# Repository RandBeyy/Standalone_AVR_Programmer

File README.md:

This project is based on Nick Gammon's ATmega_Hex_Uploader.
I added the LCD2004 to the project and design PCB so this device look more decent.
The main reason of this project is to make a small device to program a lot of MCUs like Attiny45
with simple and easy interface and without a computer.

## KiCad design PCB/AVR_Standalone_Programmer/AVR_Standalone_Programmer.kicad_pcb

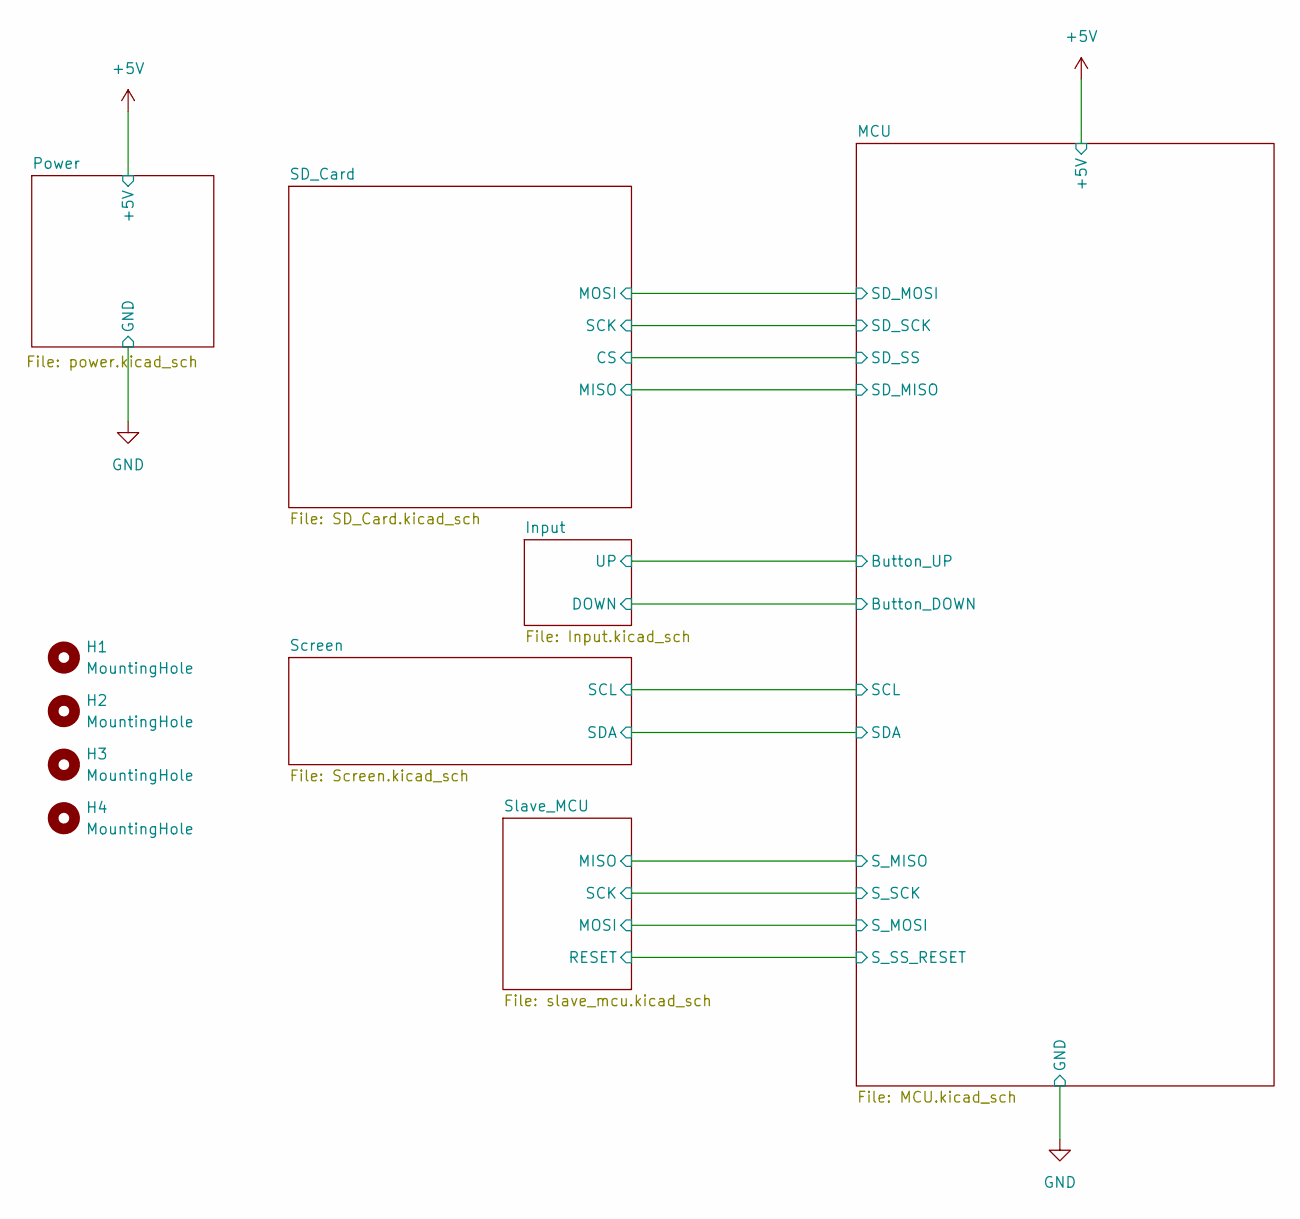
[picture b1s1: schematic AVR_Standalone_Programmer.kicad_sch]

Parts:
H1, H2, H3, H4: MountingHole; MountingHole_2.2mm_M2

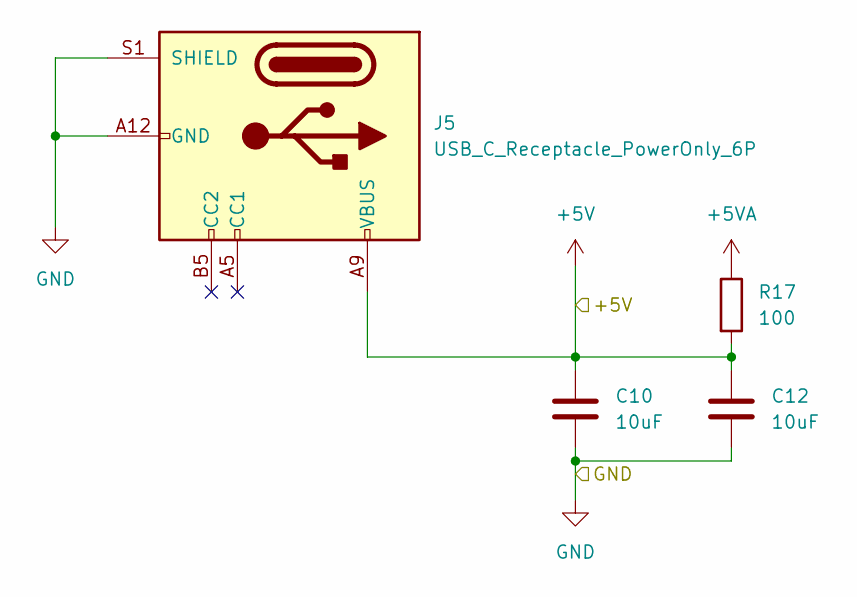
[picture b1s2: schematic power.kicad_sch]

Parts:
C10, C12: 10uF; C_0603_1608Metric
J5: USB_C_Receptacle_PowerOnly_6P; USB_C_Receptacle_GCT_USB4125-xx-x_6P_TopMnt_Horizontal
R17: 100; R_0603_1608Metric

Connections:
+5V: C10.1, C12.1, J5.A9 (VBUS), J5.B9 (VBUS), R17.2; also elsewhere on the board
+5VA: R17.1; also elsewhere on the board
GND: C10.2, C12.2, J5.A12 (GND), J5.B12 (GND), J5.S1 (SHIELD); also elsewhere on the board

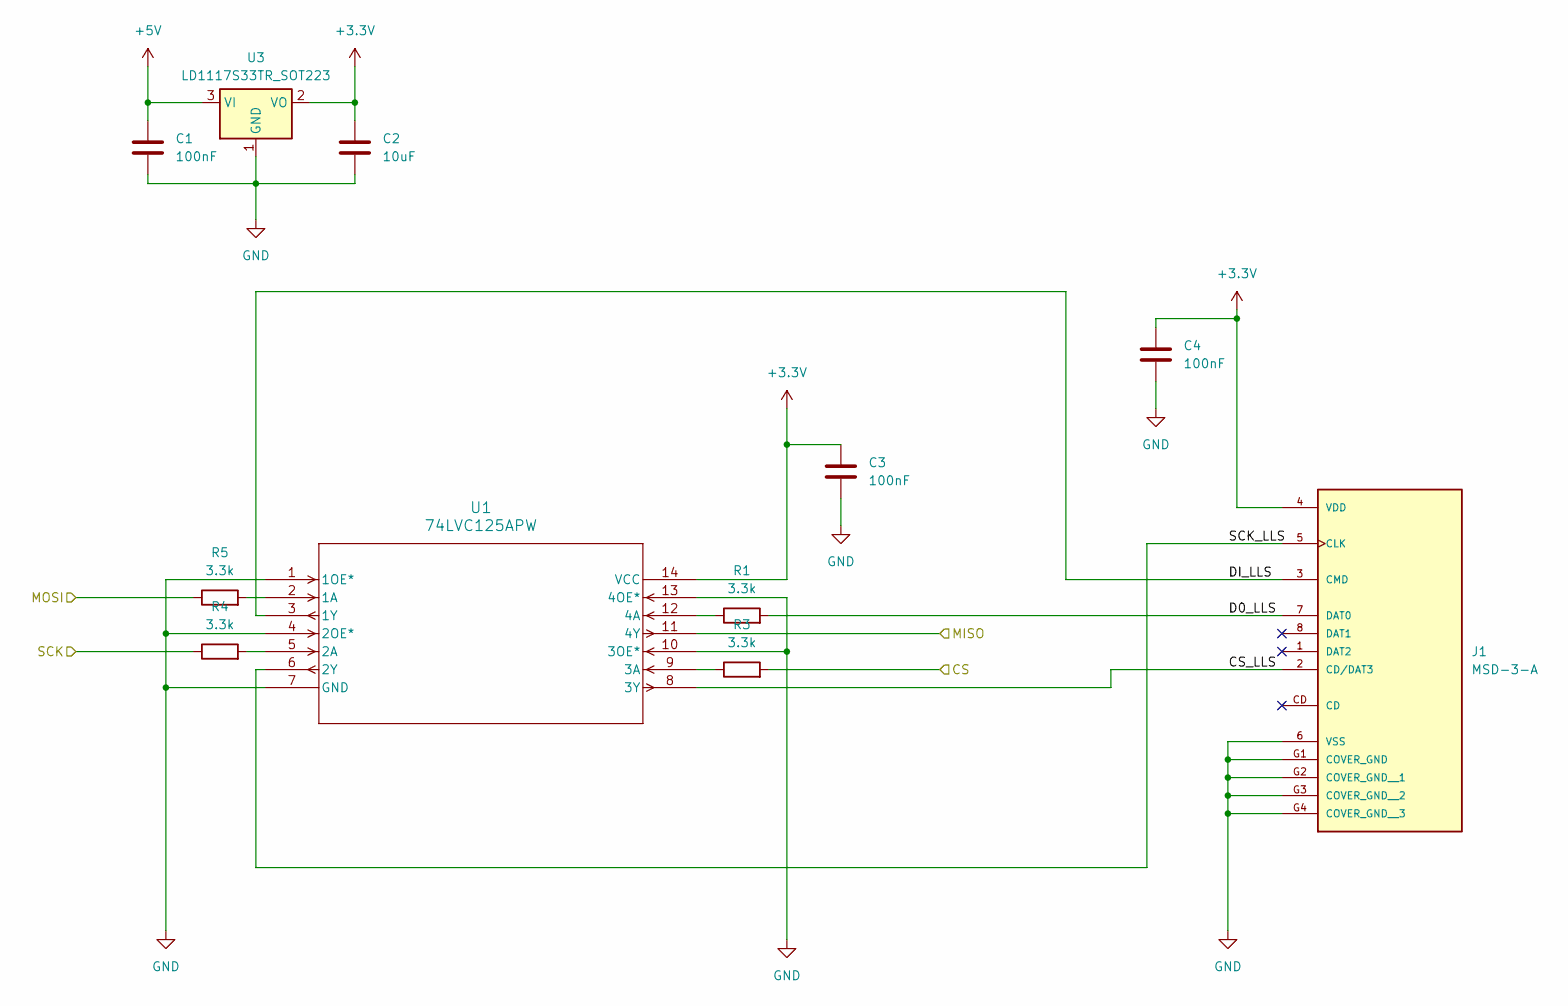
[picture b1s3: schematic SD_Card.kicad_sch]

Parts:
C1, C3, C4: 100nF; C_0603_1608Metric
C2: 10uF; C_0603_1608Metric
J1: MSD-3-A; CUI_MSD-3-A; PARTREV 1.0
R1, R3, R4, R5: 3.3k; R_0603_1608Metric
U1: 74LVC125APW; SOT402-1_NEX
U3: LD1117S33TR_SOT223; SOT-223-3_TabPin2

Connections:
+3.3V: C2.1, C3.1, C4.1, J1.4 (VDD), U1.14 (VCC), U3.2 (VO)
+5V: C1.1, U3.3 (VI); also elsewhere on the board
/MCU/MISO: U1.11 (4Y); also elsewhere on the board
/MCU/MOSI: R5.1; also elsewhere on the board
/MCU/SCK: R4.1; also elsewhere on the board
/MCU/SD_SS: R3.2; also elsewhere on the board
/SD_Card/CS_LLS: J1.2 (CD/DAT3), U1.8 (3Y)
/SD_Card/D0_LLS: J1.7 (DAT0), R1.2
/SD_Card/DI_LLS: J1.3 (CMD), U1.3 (1Y)
/SD_Card/SCK_LLS: J1.5 (CLK), U1.6 (2Y)
GND: C1.2, C2.2, C3.2, C4.2, J1.6 (VSS), J1.G1 (COVER_GND), J1.G2 (COVER_GND__1), J1.G3 (COVER_GND__2), J1.G4 (COVER_GND__3), U1.1 (1OE*), U1.4 (2OE*), U1.7 (GND), U1.10 (3OE*), U1.13 (4OE*), U3.1 (GND); also elsewhere on the board
unnamed: R5.2, U1.2 (1A)
unnamed: R4.2, U1.5 (2A)
unnamed: R3.1, U1.9 (3A)
unnamed: R1.1, U1.12 (4A)

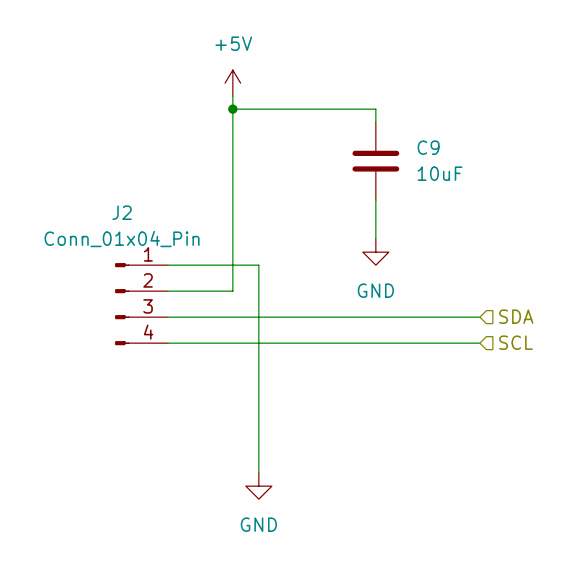
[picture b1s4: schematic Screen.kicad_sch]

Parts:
C9: 10uF; C_0603_1608Metric
J2: Conn_01x04_Pin; PinHeader_1x04_P2.54mm_Vertical

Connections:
+5V: C9.1, J2.2; also elsewhere on the board
/MCU/SCL: J2.4; also elsewhere on the board
/MCU/SDA: J2.3; also elsewhere on the board
GND: C9.2, J2.1; also elsewhere on the board

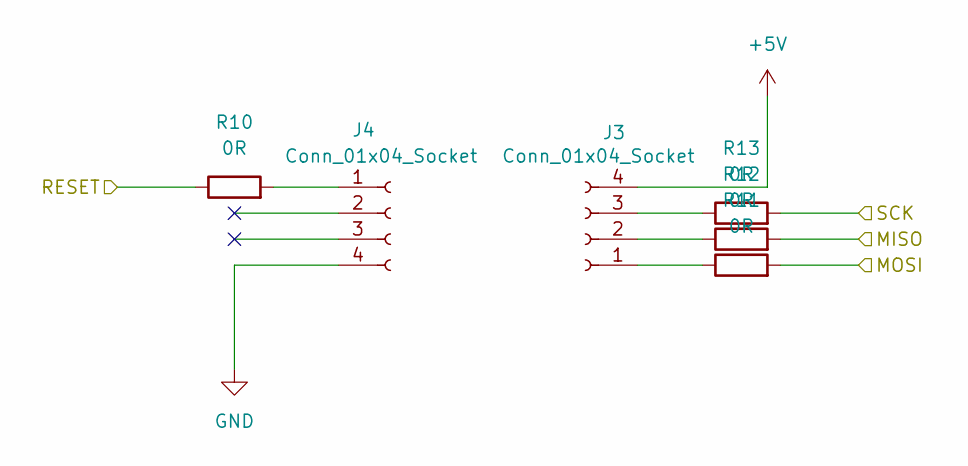
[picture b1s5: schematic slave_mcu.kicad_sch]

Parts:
J3, J4: Conn_01x04_Socket; PinSocket_1x04_P2.54mm_Vertical
R10, R11, R12, R13: 0R; R_0603_1608Metric

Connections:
+5V: J3.4; also elsewhere on the board
/MCU/S_MISO: R12.2; also elsewhere on the board
/MCU/S_MOSI: R11.2; also elsewhere on the board
/MCU/S_SCK: R13.2; also elsewhere on the board
/MCU/S_SS_RESET: R10.1; also elsewhere on the board
GND: J4.4; also elsewhere on the board
unnamed: J3.1, R11.1
unnamed: J3.2, R12.1
unnamed: J3.3, R13.1
unnamed: J4.1, R10.2

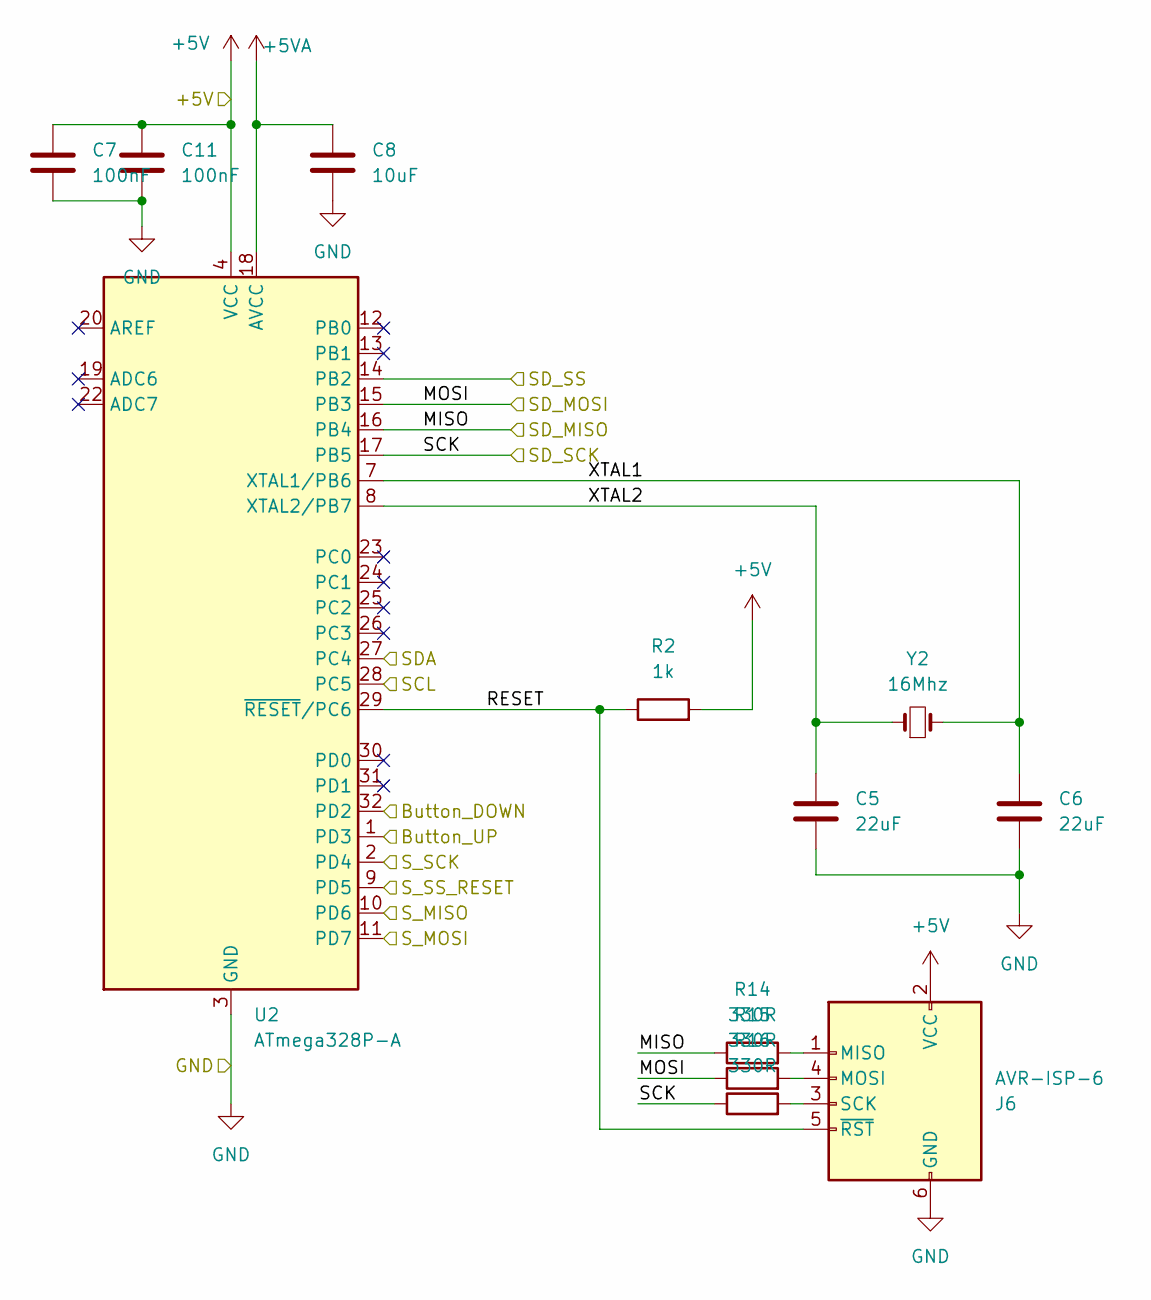
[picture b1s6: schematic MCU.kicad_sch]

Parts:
C5, C6: 22uF; C_0805_2012Metric
C7, C11: 100nF; C_0603_1608Metric
C8: 10uF; C_0603_1608Metric
J6: AVR-ISP-6; PinHeader_2x03_P2.54mm_Vertical
R2: 1k; R_0603_1608Metric
R14, R15, R16: 330R; R_0603_1608Metric
U2: ATmega328P-A; TQFP-32_7x7mm_P0.8mm
Y2: 16Mhz; Crystal_SMD_5032-2Pin_5.0x3.2mm

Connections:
+5V: C7.1, C11.1, J6.2 (VCC), R2.2, U2.4 (VCC), U2.6 (VCC); also elsewhere on the board
+5VA: C8.1, U2.18 (AVCC); also elsewhere on the board
/Input/DOWN: U2.32 (PD2); also elsewhere on the board
/Input/UP: U2.1 (PD3); also elsewhere on the board
/MCU/MISO: R14.1, U2.16 (PB4); also elsewhere on the board
/MCU/MOSI: R15.1, U2.15 (PB3); also elsewhere on the board
/MCU/RESET: J6.5 (~RST), R2.1, U2.29 (~RESET/PC6)
/MCU/SCK: R16.1, U2.17 (PB5); also elsewhere on the board
/MCU/SCL: U2.28 (PC5); also elsewhere on the board
/MCU/SDA: U2.27 (PC4); also elsewhere on the board
/MCU/SD_SS: U2.14 (PB2); also elsewhere on the board
/MCU/S_MISO: U2.10 (PD6); also elsewhere on the board
/MCU/S_MOSI: U2.11 (PD7); also elsewhere on the board
/MCU/S_SCK: U2.2 (PD4); also elsewhere on the board
/MCU/S_SS_RESET: U2.9 (PD5); also elsewhere on the board
/MCU/XTAL1: C6.1, U2.7 (XTAL1/PB6), Y2.2
/MCU/XTAL2: C5.1, U2.8 (XTAL2/PB7), Y2.1
GND: C5.2, C6.2, C7.2, C8.2, C11.2, J6.6 (GND), U2.3 (GND), U2.5 (GND), U2.21 (GND); also elsewhere on the board
unnamed: J6.1 (MISO), R14.2
unnamed: J6.4 (MOSI), R15.2
unnamed: J6.3 (SCK), R16.2

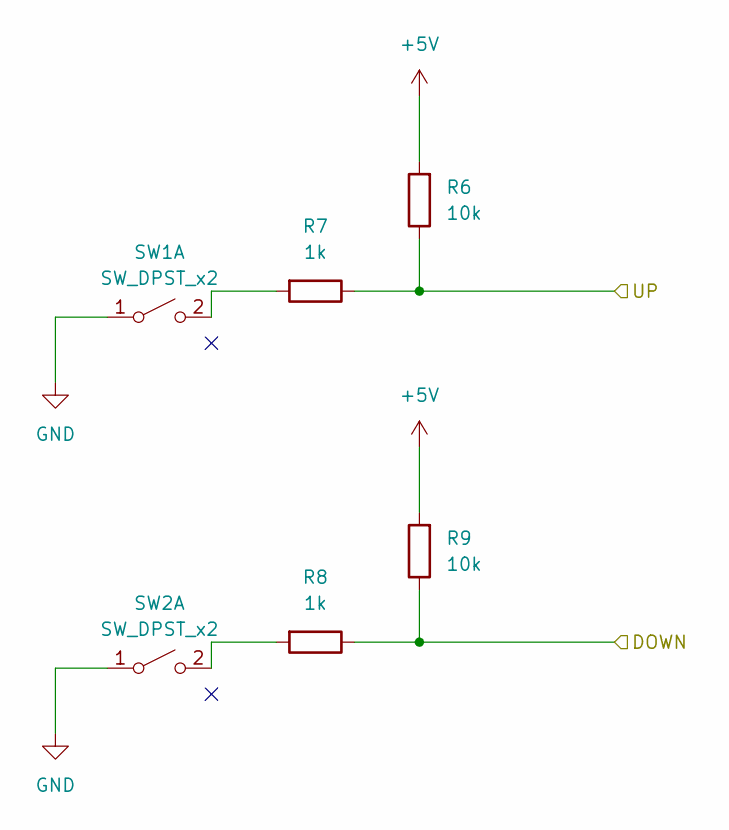
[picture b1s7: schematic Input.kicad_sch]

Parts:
R6, R9: 10k; R_0603_1608Metric
R7, R8: 1k; R_0603_1608Metric
SW1, SW2: SW_DPST_x2; SW_Push_SPST_NO_Alps_SKRK

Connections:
+5V: R6.2, R9.2; also elsewhere on the board
/Input/DOWN: R8.1, R9.1; also elsewhere on the board
/Input/UP: R6.1, R7.1; also elsewhere on the board
GND: SW1.1 (A), SW2.1 (A); also elsewhere on the board
unnamed: R7.2, SW1.2 (B)
unnamed: R8.2, SW2.2 (B)

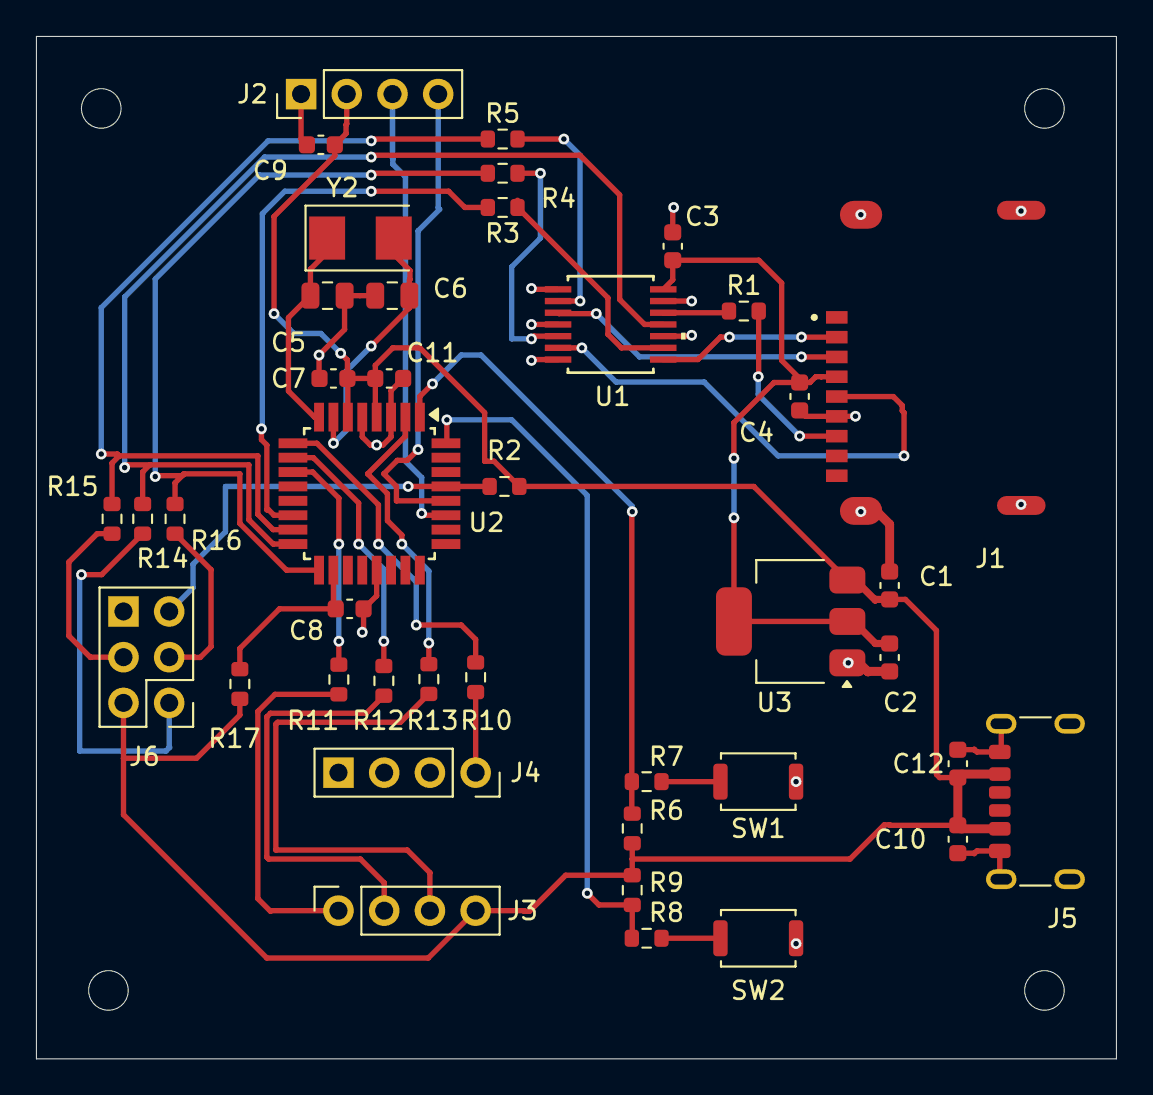
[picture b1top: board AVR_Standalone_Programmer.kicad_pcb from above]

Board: 2 copper layers, 60.0 x 56.8 mm, 45 parts (0 on the bottom side), 36 nets.

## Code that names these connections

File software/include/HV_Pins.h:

// HV_Pins.h
//
// Pin numbers and commands for high-voltage serial or parallel programming
//
// Author: Nick Gammon




#if HIGH_VOLTAGE_PARALLEL || HIGH_VOLTAGE_SERIAL

  // high-voltage programming commands we can send (when action is LOAD_COMMAND)
  enum {
        CMD_CHIP_ERASE       = 0b10000000,
        CMD_WRITE_FUSE_BITS  = 0b01000000,
        CMD_WRITE_LOCK_BITS  = 0b00100000,
        CMD_WRITE_FLASH      = 0b00010000,
        CMD_WRITE_EEPROM     = 0b00010001,
        CMD_READ_SIGNATURE   = 0b00001000,
        CMD_READ_FUSE_BITS   = 0b00000100,
        CMD_READ_FLASH       = 0b00000010,
        CMD_READ_EEPROM      = 0b00000011,
        CMD_NO_OPERATION     = 0b00000000,
        }; // end of commands

#endif // HIGH_VOLTAGE_PARALLEL || HIGH_VOLTAGE_SERIAL

#if HIGH_VOLTAGE_PARALLEL
  // pin assignments for parallel high-voltage programming
  
// Arduino pins                 Target pins
// ------------                 -----------------------
  const byte dataPins [8] = { 
    6,                        // 14 (PB0) (data bit 0)
    7,                        // 15 (PB1) (data bit 1)
    8,                        // 16 (PB2) (data bit 2)
    9,                        // 17 (PB3) (data bit 3)  
    10,                       // 18 (PB4) (data bit 4)
    11,                       // 19 (PB5) (data bit 5)  
    12,                       // 23 (PC0) (data bit 6)
    13                        // 24 (PC1) (data bit 7)
    };    // end of dataPins

  enum {                                        
      RDY     = A0,           //  3 (PD1) (low means busy)   
      OE      = A1,           //  4 (PD2) (low means output enabled)    
      WR      = A2,           //  5 (PD3) (low means write)    
      BS1     = A3,           //  6 (PD4)     
      XTAL1   = A4,           //  9 (XTAL1)     
      XA0     = A5,           // 11 (PD5)     
      XA1     =  2,           // 12 (PD6)     
      PAGEL   =  3,           // 13 (PD7)     
      BS2     =  4,           // 25 (PC2)     
      VCC     =  5,           // 7 and 20 (VCC and AVCC)
  };  // end of other pins                  
                                            
  
  /* Note: /RESET (Pin 1) is brought to 12V by connecting a transistor and MOSFET (high-side driver)
     via a RC network to (the target) VCC. R = 22k, C = 10 nF. This gives a delay of around 40 uS between
     VCC and /RESET. The transistor turns on the MOSFET, which switches +12V to /RESET.
     For transistor/MOSFET schematic see: http://www.gammon.com.au/images/Arduino/MOSFET_high_side_driver.png
     
          |------------------------------------------------------->  VCC and AVCC
          |
   D5 >---|--/\/\/\/\---|-----------> Transistor ---> MOSFET -----> /RESET
               22k      |
                       ===  10 nF
                        |
                        |
                        V
                       Gnd
       
     Also connect the grounds. Gnd to pins 8 and 22.
     Decoupling capacitors: 0.1 uF between VCC/AVCC (pins 7 and 20) and Gnd.
     Not connected on target: pins 2, 10, 21, 26, 27, 28.
  */
  
  // when XTAL1 is pulsed the settings in XA1 and XA0 control the action
  enum {
       ACTION_LOAD_ADDRESS,
       ACTION_LOAD_DATA,
       ACTION_LOAD_COMMAND,
       ACTION_IDLE
       };    // end of actions

       
#endif //  HIGH_VOLTAGE_PARALLEL

#if HIGH_VOLTAGE_SERIAL

// ATMEL ATTINY 25/45/85 / ARDUINO
//
//             +-\/-+
//    /RESET  1|    |8  VCC  
// (SCI) PB3  2|    |7  PB2 (SDO)
// (N/C) PB4  3|    |6  PB1 (SII) 
//       GND  4|    |5  PB0 (SDI)
//             +----+


// Arduino pins                                  Target pins
// ------------                                  -------------------
enum {
    VCC   = 3,  // VCC and /RESET (see above for comments)  (pin 8)
    SDI   = 4,  // Serial Data Input                --> PB0 (pin 5)
    SII   = 5,  // Serial Instruction Input         --> PB1 (pin 6)
    SDO   = 6,  // Serial Data Output               --> PB2 (pin 7)
    SCI   = 7,  // Serial Clock Input (min. 220nS)  --> PB3 (pin 2)
};

enum {
    SII_LOAD_COMMAND        = 0b01001100,
    SII_LOAD_ADDRESS_LOW    = 0b00001100,
    SII_LOAD_ADDRESS_HIGH   = 0b00011100,
    SII_READ_LOW_BYTE       = 0b01101000,
    SII_READ_HIGH_BYTE      = 0b01111000,
    SII_WRITE_LOW_BYTE      = 0b01100100,
    SII_WRITE_HIGH_BYTE     = 0b01110100,
    SII_LOAD_LOW_BYTE       = 0b00101100,
    SII_LOAD_HIGH_BYTE      = 0b00111100,
    SII_WRITE_EXTENDED_FUSE = 0b01100110,
    SII_PROGRAM_LOW_BYTE    = 0b01101101, 
    SII_PROGRAM_HIGH_BYTE   = 0b01111101,
    SII_READ_EEPROM         = 0b01101000,
    
    // various actions are latched in by ORing in this value
    SII_OR_MASK             = 0b00001100,
   
    };  // end of chip commands
        
#endif // HIGH_VOLTAGE_SERIAL

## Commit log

2024-09-14 initial comit
2024-09-23 added basic display output
2024-09-23 added read file functionality
2024-09-23 change displayHuy function to displayMessage
2024-10-01 Change OLED to LCD2004
2024-10-10 added functionality for write
2024-10-12 change arduino uno to nano
2024-11-30 turn ALLOW_FILE_SAVING false to free memory
2024-11-30 Add pcb files to directory, move all software related files to coresponding folder
2025-01-25 added message for missing MCU and 1s delay before starting
2025-01-25 added readme.md
